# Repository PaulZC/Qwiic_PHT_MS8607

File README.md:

# Qwiic PHT MS8607

### We've moved!

This repo has a new home over at [SparkFun](https://github.com/sparkfun/Qwiic_PHT_MS8607)

_"So long, and thanks for all the fish."_
_(Douglas Adams)_

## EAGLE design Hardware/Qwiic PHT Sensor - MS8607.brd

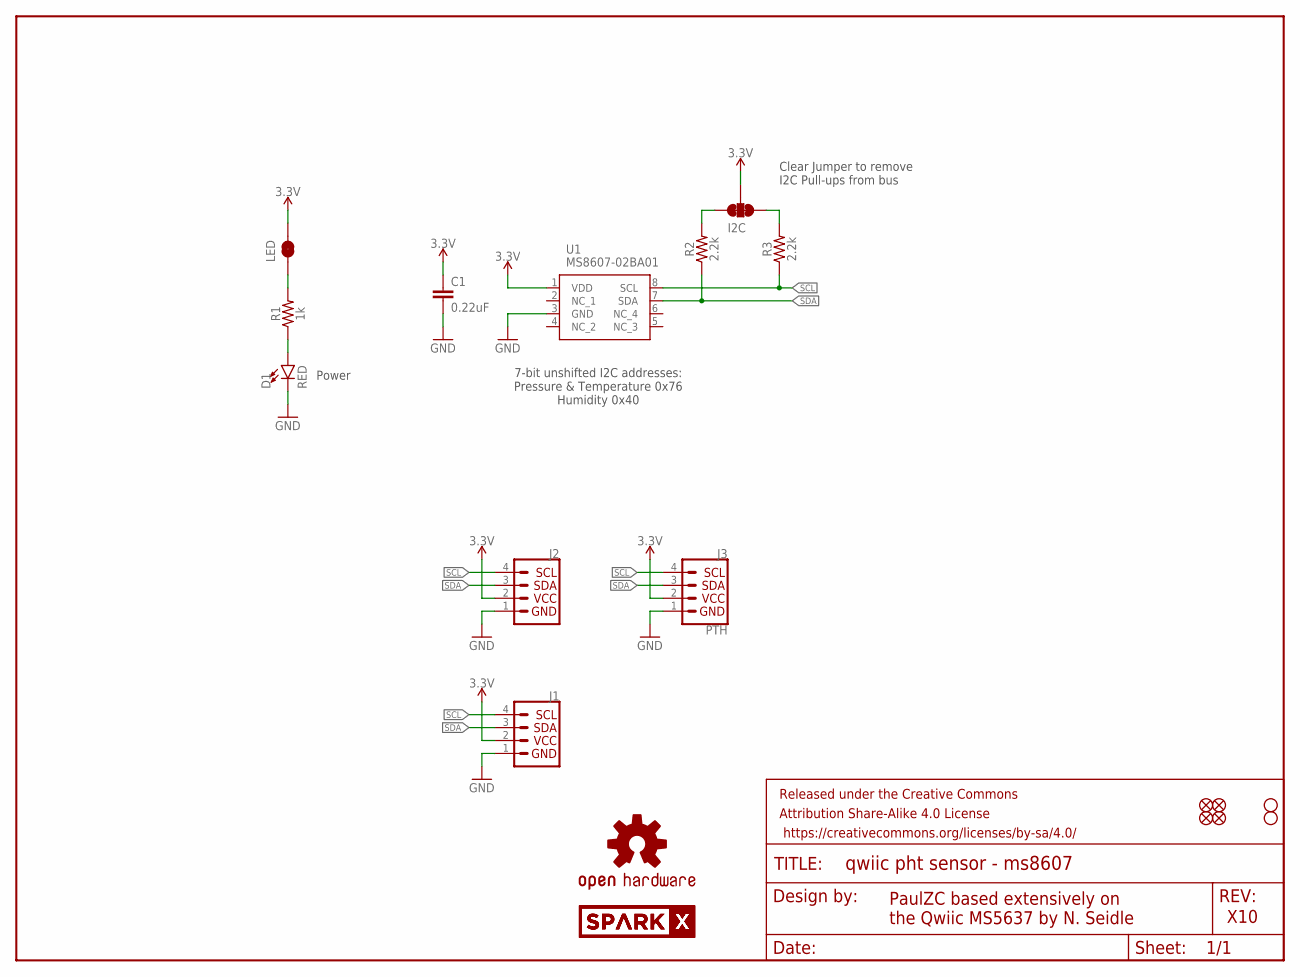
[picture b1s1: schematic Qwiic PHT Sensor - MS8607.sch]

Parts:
C1: 0.22uF; 0603
D1: RED; LED-0603
FRAME1: FRAME-LETTER; CREATIVE_COMMONS
I2C: JUMPER-SMT_3_2-NC_TRACE_SILK; SMT-JUMPER_3_2-NC_TRACE_SILK
J1, J2: I2C_STANDARDQWIIC; 1X04_1MM_RA
J3: PTH; 1X04_NO_SILK
JP1, JP2, JP5, JP6: FIDUCIALUFIDUCIAL; MICRO-FIDUCIAL
JP3, JP4: STAND-OFF
LED: JUMPER-SMT_2_NC_TRACE_SILK; SMT-JUMPER_2_NC_TRACE_SILK
LOGO1: OSHW-LOGOMINI; OSHW-LOGO-MINI
R1: 1k; 0603
R2, R3: 2.2k; 0603
U1: MS8607-02BA01
U$1, U$2: SPARKX-LOGO4; SPARKX-MEDIUM

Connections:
3.3V: C1.1, I2C.2, J1.2, J2.2, J3.2 (VCC), LED.2, U1.1 (VDD)
GND: C1.2, D1.C, J1.1, J2.1, J3.1 (GND), U1.3 (GND)
unnamed: I2C.1, R3.2
unnamed: I2C.3, R2.2
unnamed: D1.A, R1.1
unnamed: LED.1, R1.2
SCL: J1.4, J2.4, J3.4 (SCL), R3.1, U1.8 (SCL)
SDA: J1.3, J2.3, J3.3 (SDA), R2.1, U1.7 (SDA)

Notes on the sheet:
PaulZC based extensively on the Qwiic MS5637 by N. Seidle
X10
7-bit unshifted I2C addresses: Pressure & Temperature 0x76 Humidity 0x40
Clear Jumper to remove I2C Pull-ups from bus
Power

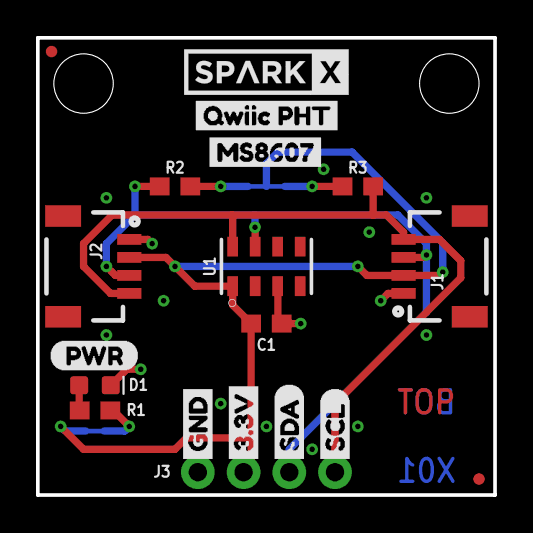
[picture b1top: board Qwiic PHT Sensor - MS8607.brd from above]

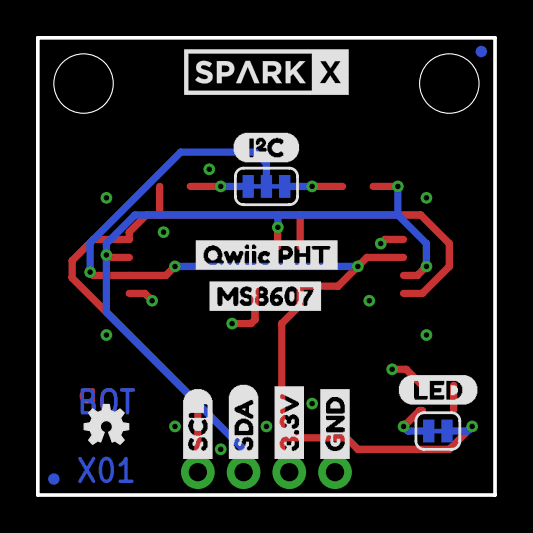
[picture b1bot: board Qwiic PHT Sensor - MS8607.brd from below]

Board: 2 copper layers, 25.4 x 25.4 mm, 36 parts (14 on the bottom side), 8 nets.

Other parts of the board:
U$3, U$22: GND1
U$4, U$21: 3#3V2
U$5, U$27: SDA8
U$6, U$26: SCL9
U$9, U$12: QWIIC_PHT0
U$10: (PWR)
U$11: (I_SUPER2_C)
U$15, U$16: MS86070
U$17: LED0

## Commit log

2019-11-01 Added the restrict area between the MS8607 pins
2019-11-28 Added the PCB image
2020-05-30 Added the link to the SparkFun repo

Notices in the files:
parts and their libraries:
SparkFun-Resistors: Licensing: Creative Commons ShareAlike 4.0 International - https://creativecommons.org/licenses/by-sa/4.0
SparkFun-Aesthetics: Released under the Creative Commons Attribution Share-Alike 4.0 License
SparkFun-Aesthetics: https://creativecommons.org/licenses/by-sa/4.0
